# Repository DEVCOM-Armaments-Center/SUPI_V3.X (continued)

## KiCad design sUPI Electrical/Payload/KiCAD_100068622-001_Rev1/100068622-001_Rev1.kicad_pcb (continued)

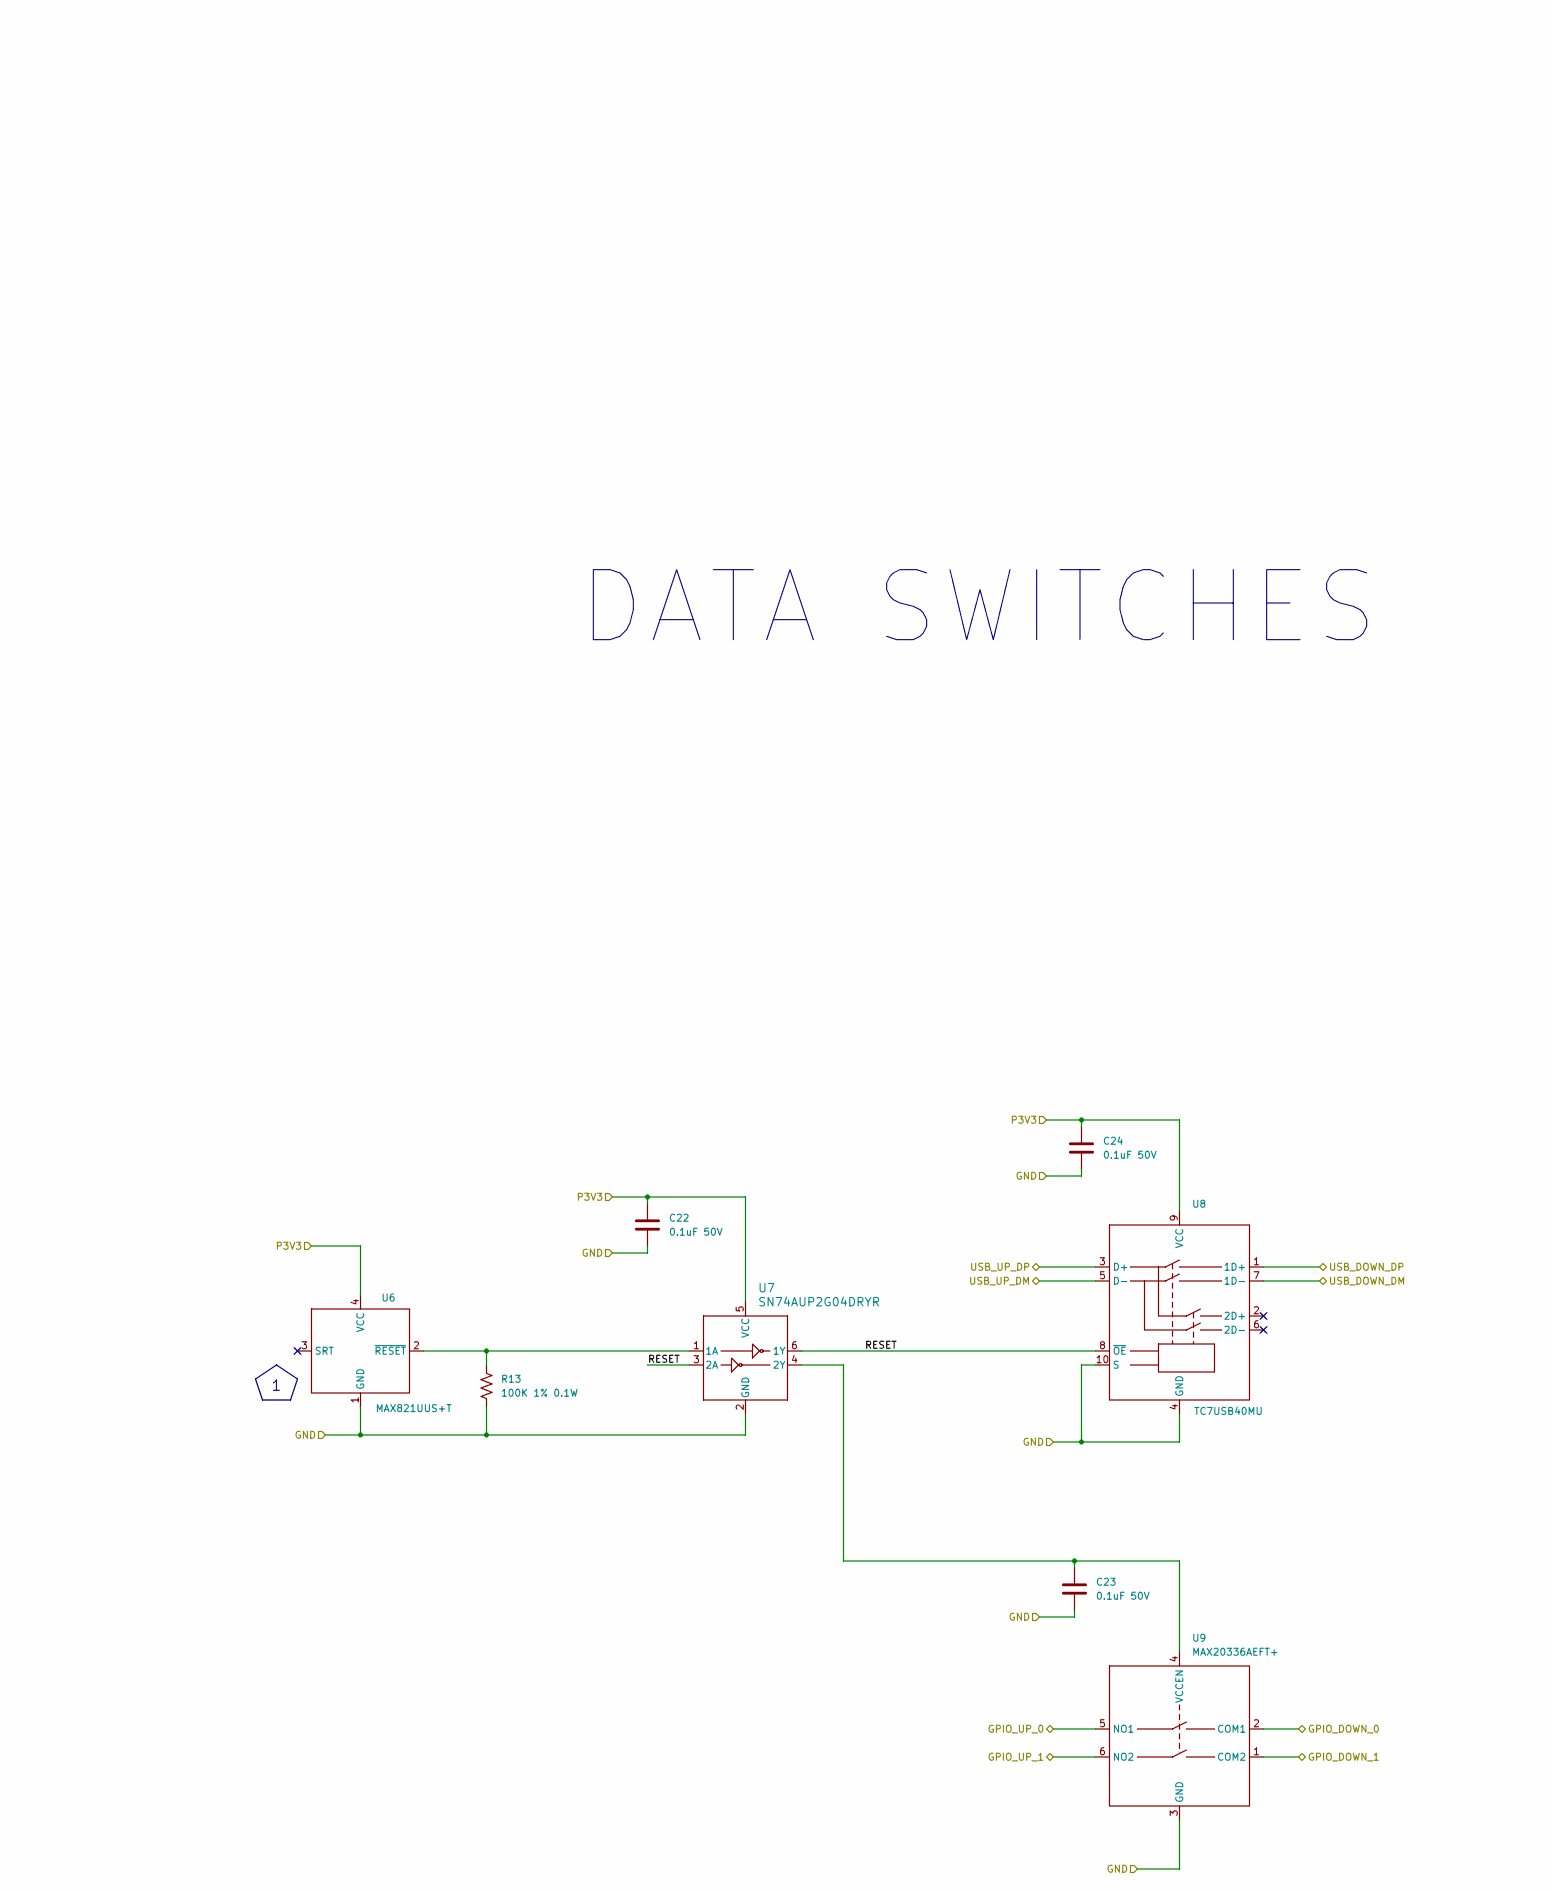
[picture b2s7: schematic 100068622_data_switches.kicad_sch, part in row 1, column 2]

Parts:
C22, C23, C24: 0.1uF 50V; C_0402_1005Metric; MPN GCM155R71H104ME02D
R13: 100K 1% 0.1W; R_0402_1005Metric; MPN ERJ-2RKF1003X
U6: SOT-143 Maxim; MPN MAX821UUS+T
U7: SN74AUP2G04DRYR; QFN-6_1.4x1mm_P0.5mm TI DRY6; MPN SN74AUP3G04DQER
U8: Toshiba UQFN-10_1.4x1.8mm_P0.4mm; MPN TC7USB40MU
U9: FC2QFN-6; MPN MAX20336AEFT+

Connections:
/Block Diagram/Data Switches/GPIO_DOWN_0: U9.2 (COM1); also elsewhere on the board
/Block Diagram/Data Switches/GPIO_DOWN_1: U9.1 (COM2); also elsewhere on the board
/Block Diagram/Data Switches/RESET: U7.3 (2A), U7.6 (1Y), U8.8 (~OE)
/Block Diagram/Data Switches/USB_DOWN_DM: U8.7 (1D-); also elsewhere on the board
/Block Diagram/Data Switches/USB_DOWN_DP: U8.1 (1D+); also elsewhere on the board
/Block Diagram/GPIO0: U9.5 (NO1); also elsewhere on the board
/Block Diagram/GPIO1: U9.6 (NO2); also elsewhere on the board
/Block Diagram/Power Supplies/P3V3_AUX: C22.1, C24.1, U6.4 (VCC), U7.5 (VCC), U8.9 (VCC); also elsewhere on the board
/Block Diagram/USB_D+: U8.3 (D+); also elsewhere on the board
/Block Diagram/USB_D-: U8.5 (D-); also elsewhere on the board
GND: C22.2, C23.2, C24.2, R13.2, U6.1 (GND), U7.2 (GND), U8.4 (GND), U8.10 (S), U9.3 (GND); also elsewhere on the board
unnamed: R13.1, U6.2 (~RESET), U7.1 (1A)
unnamed: C23.1, U7.4 (2Y), U9.4 (VCCEN)

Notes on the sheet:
DESIGN NOTES
DATA SWITCHES
POWER-ON RESET DELAY IS 100MS MINIMUM, 200MS MAXIMUM, 160MS TYPICAL. SWITCHES WILL DISCONNECT AS SOON AS 3.3V AUX RAIL DROPS BELOW THRESHOLD VOLTAGE.

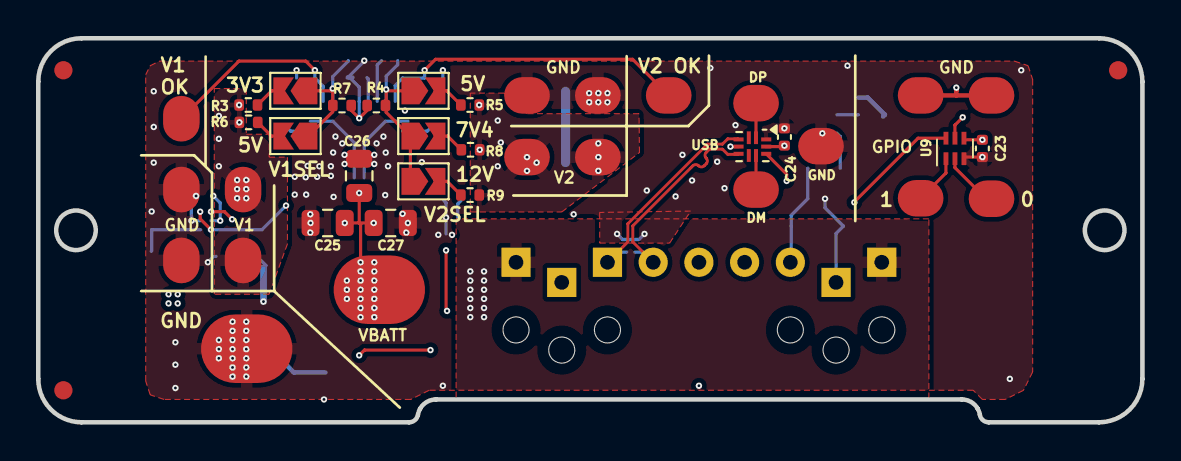
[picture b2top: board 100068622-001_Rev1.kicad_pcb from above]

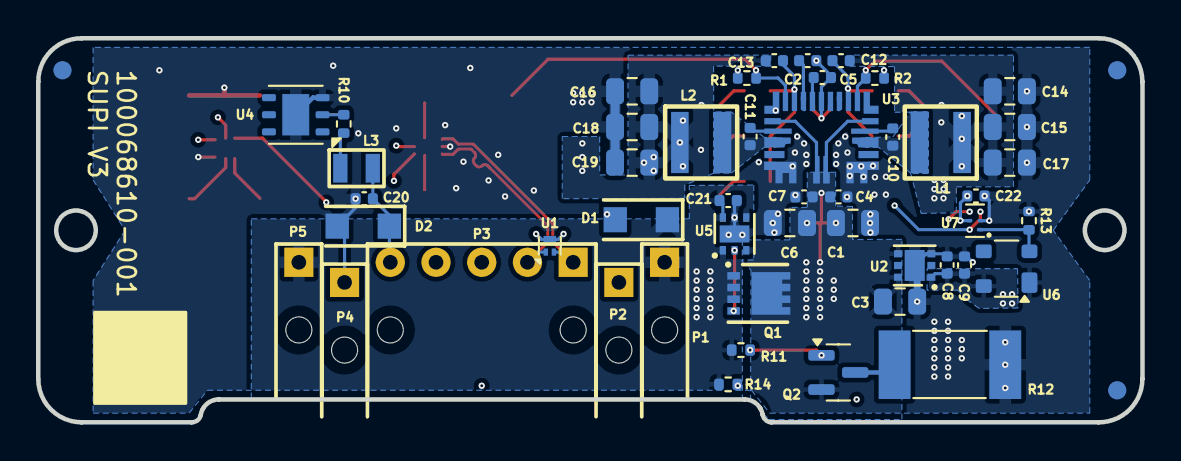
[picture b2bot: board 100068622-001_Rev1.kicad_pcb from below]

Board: 4 copper layers, 61.3 x 21.3 mm, 94 parts (52 on the bottom side), 40 nets.

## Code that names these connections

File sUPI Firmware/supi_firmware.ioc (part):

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Mcu.Name=STM32C011F(4-6)Ux
Mcu.Package=UFQFPN20
Mcu.UserName=STM32C011F6Ux
PA0.GPIOParameters=GPIO_Label
PA0.GPIO_Label=LS_ENABLE
PA0.Signal=GPIO_Output
PA1.GPIOParameters=GPIO_Label
PA1.GPIO_Label=LS_IMON
PA1.Mode=IN1
PA1.Signal=ADC1_IN1
PA13.Mode=Serial_Wire
PA13.Signal=DEBUG_SWDIO
PA14-BOOT0.Mode=Serial_Wire
PA14-BOOT0.Signal=DEBUG_SWCLK
PA3.GPIOParameters=GPIO_Label
PA3.GPIO_Label=DETECT
PA3.Signal=S_TIM1_CH4
PA4.GPIOParameters=GPIO_Label,GPIO_ModeDefaultEXTI
PA4.GPIO_Label=LS_FAULT
PA4.GPIO_ModeDefaultEXTI=GPIO_MODE_IT_RISING
PA4.Signal=GPXTI4
PA5.GPIOParameters=GPIO_Label
PA5.GPIO_Label=LS_POWER_GOOD
PA5.Signal=GPXTI5
PA6.GPIOParameters=GPIO_Label
PA6.GPIO_Label=I_SNS
PA6.Mode=IN6
PA6.Signal=ADC1_IN6
PA7.GPIOParameters=GPIO_Label
PA7.GPIO_Label=I_FAULT
PA7.Signal=GPXTI7
PB6.GPIOParameters=GPIO_Speed,GPIO_FM6,GPIO_Label
PB6.GPIO_FM6=SYSCFG_FASTMODEPLUS_PB6
PB6.GPIO_Label=STATUS
PB6.GPIO_Speed=GPIO_SPEED_FREQ_VERY_HIGH
PB6.Signal=GPIO_Output
PB7.GPIOParameters=GPIO_PuPd,GPIO_Label
PB7.GPIO_Label=CCAREV2
PB7.GPIO_PuPd=GPIO_PULLDOWN
PB7.Signal=GPIO_Input
PC14-OSCX_IN\ (PC14).GPIOParameters=GPIO_PuPd,GPIO_Label
PC14-OSCX_IN\ (PC14).GPIO_Label=CCAREV1
PC14-OSCX_IN\ (PC14).GPIO_PuPd=GPIO_PULLDOWN
PC14-OSCX_IN\ (PC14).Signal=GPIO_Input
PC15-OSCX_OUT\ (PC15).GPIOParameters=GPIO_PuPd,GPIO_Label
PC15-OSCX_OUT\ (PC15).GPIO_Label=CCAREV0
PC15-OSCX_OUT\ (PC15).GPIO_PuPd=GPIO_PULLDOWN
PC15-OSCX_OUT\ (PC15).Signal=GPIO_Input
RCC.HSE_VALUE=8000000
RCC.SYSCLKFreq_VALUE=48000000
board=custom
